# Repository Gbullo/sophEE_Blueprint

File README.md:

# sophEE_Blueprint
Fork of the esp8266-robot repository to test as potential sophEE project

Code will interface with dual h-bridge drivers instead of using adafruit libraries and shield.

Eagle .lbr files must be downloaded by saving the RAW file.

# TODO:
* Add stop button
* Finish button functionalities
* Customize UI
* Add hotspot instructions and files

# Useful links:
http://esp8266.github.io/Arduino/versions/2.0.0/doc/reference.html
https://openhomeautomation.net/build-wifi-controlled-robot-esp8266h

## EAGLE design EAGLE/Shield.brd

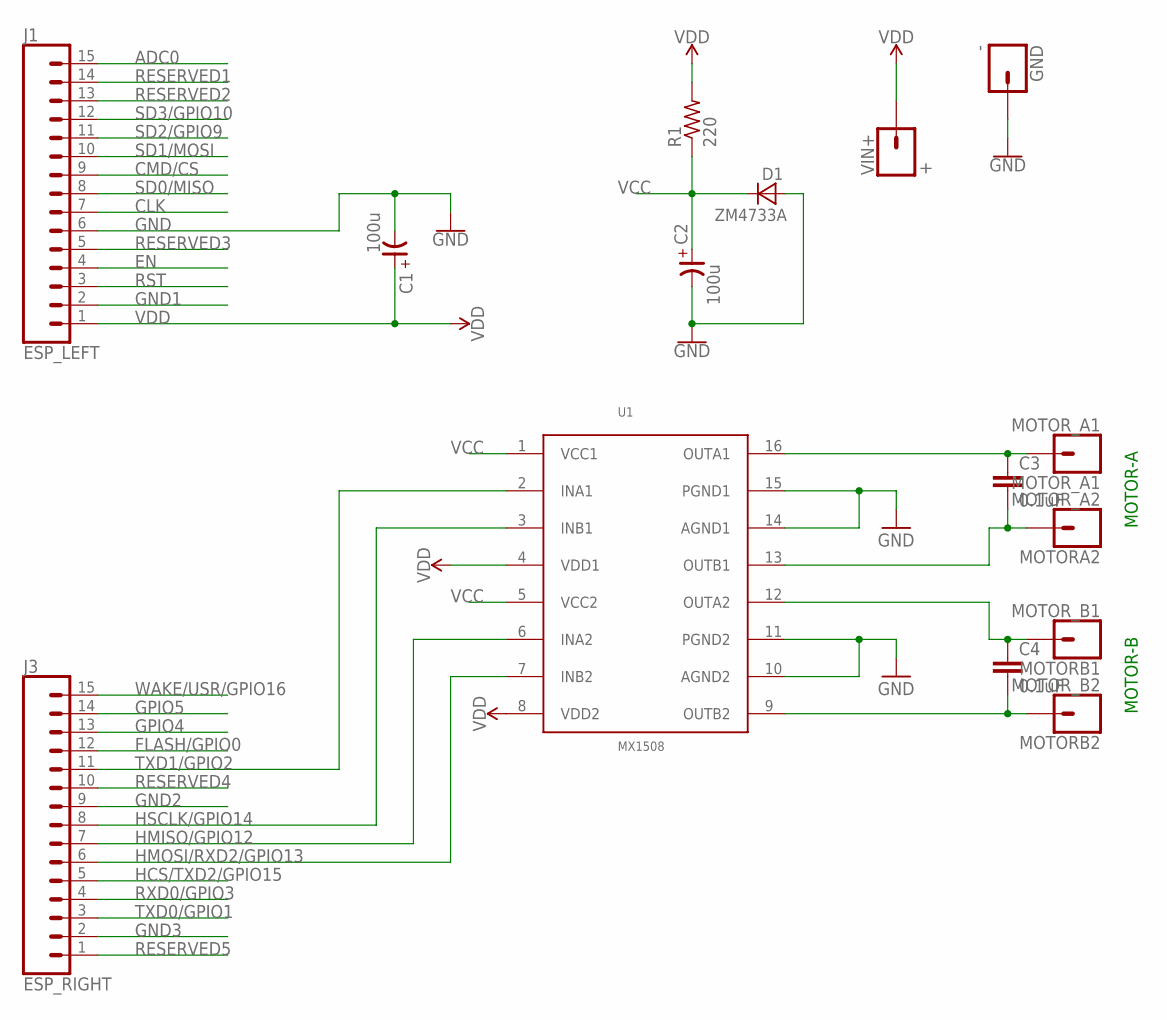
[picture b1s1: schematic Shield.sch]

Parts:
C1, C2: 100u; SV-D
C3, C4: 0.1uF; CAP-PTH-SMALL-KIT
D1: ZM4733A; MELF-MLL41
GND: -; 1X01
J1: ESP_LEFT; 1X15
J3: ESP_RIGHT; 1X15
MOTORA2: MOTOR_A2; 1X01
MOTORB1: MOTOR_B1; 1X01
MOTORB2: MOTOR_B2; 1X01
MOTOR_A1: MOTOR_A1; 1X01
R1: 220; R2512
U1: MX1508
VIN+: +; 1X01

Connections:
ADC0: J1.15
CLK: J1.7
CMD/CS: J1.9
EN: J1.4
FLASH/GPIO0: J3.12
GND: C1.-, C2.-, D1.A, GND.1, J1.6, U1.10 (AGND2), U1.11 (PGND2), U1.14 (AGND1), U1.15 (PGND1)
GND1: J1.2
GND2: J3.9
GND3: J3.2
GPIO4: J3.13
GPIO5: J3.14
HCS/TXD2/GPIO15: J3.5
HMISO/GPIO12: J3.7, U1.6 (INA2)
HMOSI/RXD2/GPIO13: J3.6, U1.7 (INB2)
HSCLK/GPIO14: J3.8, U1.3 (INB1)
unnamed: C3.1, MOTOR_A1.1, U1.16 (OUTA1)
unnamed: C3.2, MOTORA2.1, U1.13 (OUTB1)
unnamed: C4.1, MOTORB1.1, U1.12 (OUTA2)
unnamed: C4.2, MOTORB2.1, U1.9 (OUTB2)
RESERVED1: J1.14
RESERVED2: J1.13
RESERVED3: J1.5
RESERVED4: J3.10
RESERVED5: J3.1
RST: J1.3
RXD0/GPIO3: J3.4
SD0/MISO: J1.8
SD1/MOSI: J1.10
SD2/GPIO9: J1.11
SD3/GPIO10: J1.12
TXD0/GPIO1: J3.3
TXD1/GPIO2: J3.11, U1.2 (INA1)
VCC: C2.+, D1.C, R1.1, U1.1 (VCC1), U1.5 (VCC2)
VDD: C1.+, J1.1, R1.2, U1.4 (VDD1), U1.8 (VDD2), VIN+.1
WAKE/USR/GPIO16: J3.15

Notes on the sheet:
MOTOR-A
MOTOR-B

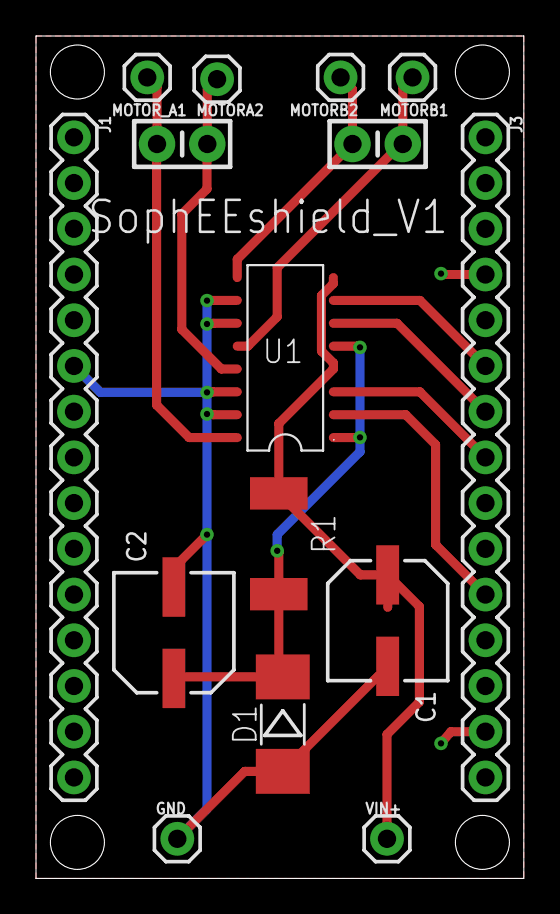
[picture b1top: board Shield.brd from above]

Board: 2 copper layers, 27.1 x 46.8 mm, 15 parts (0 on the bottom side), 11 nets.

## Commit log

2018-02-03 Added student .ino template + finished code
2018-02-03 Removed stop from script
2018-02-03 Readme update
2018-02-08 added Documentation
2018-02-17 added mx.lbr
2018-02-24 increased mx pad length
2018-02-24 Tuned control buttons for first prototype

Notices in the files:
parts and their libraries:
SparkFun-Capacitors: Licensing: Creative Commons ShareAlike 4.0 International - https://creativecommons.org/licenses/by-sa/4.0
